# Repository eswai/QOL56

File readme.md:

# QOL56

## 特徴

QOL56は、ほぼ直交格子配列(ortholinear)な56キーのキーボードです。
ortholinearキーボードはplanckが有名ですが、planckよりも2列、8キー多い配列です。
親指で自然に押せるキーを6キー配置すると必然的に14列必要になりました。
その結果、親指でシフト、スペース、エンター、レイヤー切り替えなど頻度の高いキー操作が可能です。
また、親指シフト入力での使用を念頭において設計しており、現在の親指シフト入力をする上での様々な課題を解決し、最新のキーボードトレンドを取り込んで、接続するだけで快適に親指シフト入力できることを目指すキーボードです。

## 親指シフト入力に対応

親指シフト入力のユーザーは、高価な専用キーボードを購入したり、いわゆるB割れしているキーボードを探したり、orz配列という右手のキーを1列ずらすなどの努力をしていますが、自作することで親指シフトに最適なキーボードを実現することが目的です。
同時に旧来のrow staggeredの非対称キー配置から脱却し、より効率の良い配列へ移行することもめざしています。
親指シフトなどの同時押しでは特にキー配置が左右対称であるべきだと考えています。
もっとエルゴノミックなキー配列はたくさんあるのですが、まずはシンプルで扱いやすそうな直交格子配列にしてみました。
親指との同時押しが快適にできるように親指で押す6キーを0.25U下げて配置しています。

さらに親指シフト入力をするために通常は追加でソフトウェアのインストールが必要です。
親指シフトするためのソフトとして、例えばやまぶきRやLacailleなどのソフトがあります。
自作キーボード用のファームウェアQMKは非常に高機能なので、ファームウェアレベルでの親指シフト入力をサポートしました。
追加ソフトなしでの親指シフトの入力が可能です。

## LED

バックライトやアンダーグロウのLEDはかっこよくて所有欲を満たしてくれるものですので、71個(バックライト56個、アンダーグロー15個)のフルカラーLEDを搭載して、QMKのアニメーションをフルに楽しめるようになっています。

## 実装面での特徴

* Pro Microをキー下に配置してフットプリントを最小化
* Pro Microと重ならない54キーはソケットを採用してキースイッチを交換可能にした
* コンスルー対応で、Pro Microの脱着が可能
* チルトさせることで全体が厚くならないように配慮

## 制作について

キット販売などはないので、PCBなどの部品をメーカーに制作してもらう必要がありますが、ガーバーファイルやアクリルカットのためのepsファイルを公開しています。
決して初心者向きではありませんが、ある程度知識があれば容易に部品の調達は可能です。

部品一覧表

|部品名|仕様|数量|
|---|---|---|
|PCBトッププレート|1.6mm|1|
|PCB基板|1.6mm|1|
|アクリルボトムプレート3種類|2mm|1 set|
|キースイッチ|MX互換|56|
|キーキャップ|1U|56|
|ねじ|M2 x 4mm|12|
|ねじ|M2 x 10mm|4|
|スペーサ|M2 x 7mm|8|
|Pro Micro|ATmega32U4 5V 16MHz|1|
|ダイオード|1N4148Wまたは1N4148|56|
|Kailh PCB Socket|CPG151101S11|54|
|タクトスイッチ|2極 SMD 4x3x2mm|1|

LEDを付ける場合は以下の部品を用意します。なくても動作します。

|部品名|仕様|数量|
|---|---|---|
|LED|SK6812 mini 3535|56|
|LEDテープ|WS2812|25cm 15個|

参考価格ですが、elecrowにPCB、トッププレート、ボトムプレートの3点をオーダーしましたが、最小単位の5セット、送料込みで$100以下でした。
他にはCherry MX互換のスイッチ、キーキャップ、Pro Micro、ダイオード、ソケット、M2ねじなど自作キーボードでは一般的な部品を採用しています。
また、kicadファイルも公開していますので、自由に改造して自分好みのレイアウトを作っていただくことも可能です。
QMKのコードは [GitHub](https://github.com/eswai/qmk_firmware/tree/master/keyboards/eswai/qol56) にありますので、キーマップの修正が可能です。

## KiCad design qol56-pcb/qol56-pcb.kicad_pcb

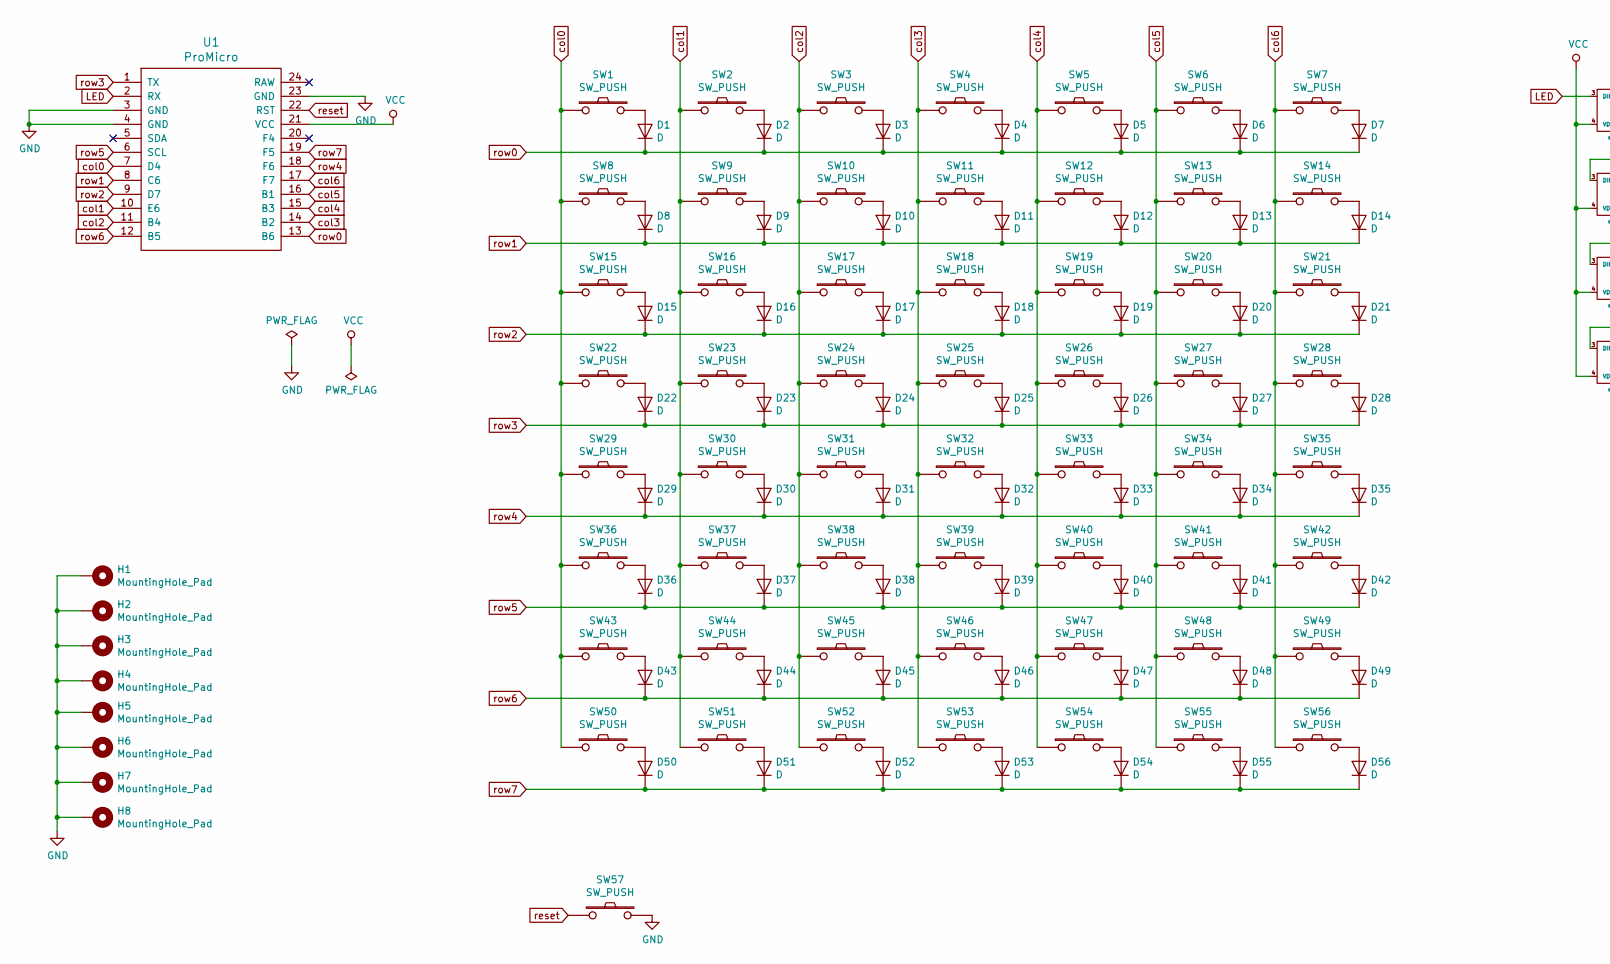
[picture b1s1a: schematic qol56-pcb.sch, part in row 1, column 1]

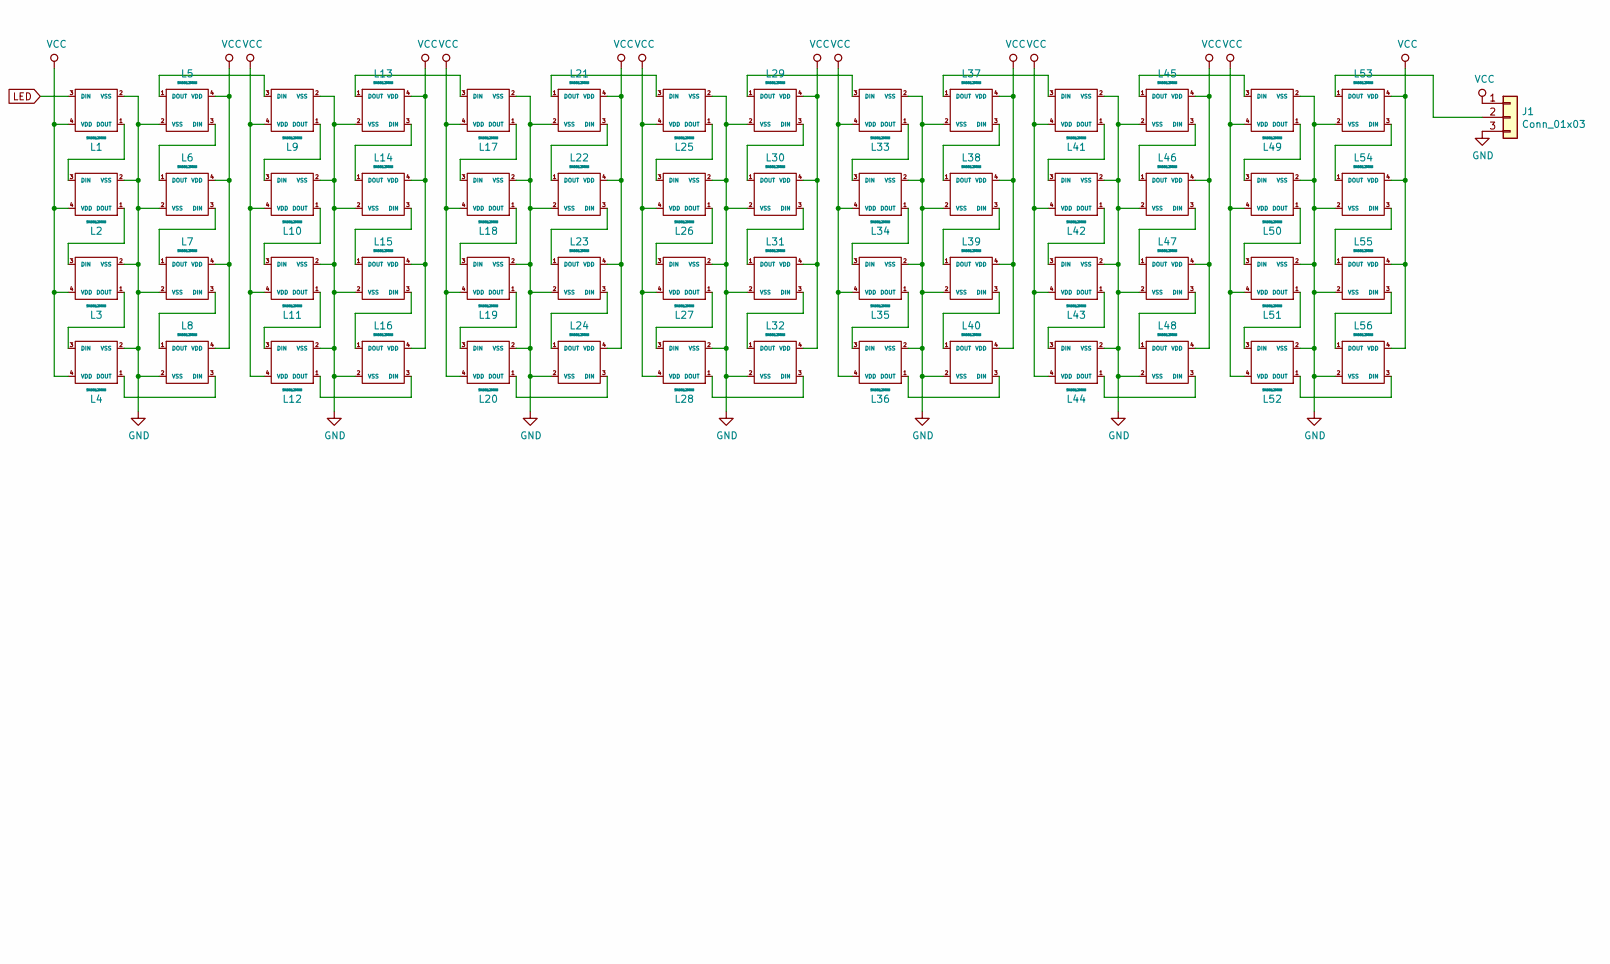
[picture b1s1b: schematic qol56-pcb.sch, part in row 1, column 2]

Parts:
D1, D2, D3, D4, D5, D6, D7, D8, D9, D10, D11, D12, D13, D14, D15, D16, D17, D18, D19, D20, D21, D22, D23, D24, D25, D26, D27, D28, D29, D30, D31, D32, D33, D34, D35, D36, D37, D38, D39, D40, D41, D42, D43, D44, D45, D46, D47, D48, D49, D50, D51, D52, D53, D54, D55, D56: D; Diode-dual
H1, H2, H3, H4, H5, H6, H7, H8: MountingHole_Pad; MountingHole_4mm_Pad
J1: Conn_01x03; StripLED_rev
L1, L2, L3, L4, L5, L6, L7, L8, L9, L10, L11, L12, L13, L14, L15, L16, L17, L18, L19, L20, L21, L22, L23, L24, L25, L26, L27, L28, L29, L30, L31, L32, L33, L34, L35, L36, L37, L38, L39, L40, L41, L42, L43, L44, L45, L46, L47, L48, L49, L50, L51, L52, L53, L54, L55, L56: SK6812MINI; SK6812MINI_rev
SW1, SW2: SW_PUSH; MX_PCB_100H
SW3, SW4, SW5, SW6, SW7, SW8, SW9, SW10, SW11, SW12, SW13, SW14, SW15, SW16, SW17, SW18, SW19, SW20, SW21, SW22, SW23, SW24, SW25, SW26, SW27, SW28, SW29, SW30, SW31, SW32, SW33, SW34, SW35, SW36, SW37, SW38, SW39, SW40, SW41, SW42, SW43, SW44, SW45, SW46, SW47, SW48, SW49, SW50, SW51, SW52, SW53, SW54, SW55, SW56: SW_PUSH; CherryMX_Hotswap
SW57: SW_PUSH; SMD 2Pin 3X4MM Tactile Tact Push Button
U1: ProMicro; ArduinoProMicro

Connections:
GND: H1.1, H2.1, H3.1, H4.1, H5.1, H6.1, H7.1, H8.1, J1.3, L1.2 (VSS), L2.2 (VSS), L3.2 (VSS), L4.2 (VSS), L5.2 (VSS), L6.2 (VSS), L7.2 (VSS), L8.2 (VSS), L9.2 (VSS), L10.2 (VSS), L11.2 (VSS), L12.2 (VSS), L13.2 (VSS), L14.2 (VSS), L15.2 (VSS), L16.2 (VSS), L17.2 (VSS), L18.2 (VSS), L19.2 (VSS), L20.2 (VSS), L21.2 (VSS), L22.2 (VSS), L23.2 (VSS), L24.2 (VSS), L25.2 (VSS), L26.2 (VSS), L27.2 (VSS), L28.2 (VSS), L29.2 (VSS), L30.2 (VSS), L31.2 (VSS), L32.2 (VSS), L33.2 (VSS), L34.2 (VSS), L35.2 (VSS), L36.2 (VSS), L37.2 (VSS), L38.2 (VSS), L39.2 (VSS), L40.2 (VSS), L41.2 (VSS), L42.2 (VSS), L43.2 (VSS), L44.2 (VSS), L45.2 (VSS), L46.2 (VSS), L47.2 (VSS), L48.2 (VSS), L49.2 (VSS), L50.2 (VSS), L51.2 (VSS), L52.2 (VSS), L53.2 (VSS), L54.2 (VSS), L55.2 (VSS), L56.2 (VSS), SW57.2, U1.3 (GND), U1.4 (GND), U1.23 (GND)
LED: L1.3 (DIN), U1.2 (RX)
unnamed: D1.2 (A), SW1.2
unnamed: D2.2 (A), SW2.2
unnamed: D3.2 (A), SW3.2
unnamed: D4.2 (A), SW4.2
unnamed: D5.2 (A), SW5.2
unnamed: D6.2 (A), SW6.2
unnamed: D7.2 (A), SW7.2
unnamed: D8.2 (A), SW8.2
unnamed: D9.2 (A), SW9.2
unnamed: D10.2 (A), SW10.2
unnamed: D11.2 (A), SW11.2
unnamed: D12.2 (A), SW12.2
unnamed: D13.2 (A), SW13.2
unnamed: D14.2 (A), SW14.2
unnamed: D15.2 (A), SW15.2
unnamed: D16.2 (A), SW16.2
unnamed: D17.2 (A), SW17.2
unnamed: D18.2 (A), SW18.2
unnamed: D19.2 (A), SW19.2
unnamed: D20.2 (A), SW20.2
unnamed: D21.2 (A), SW21.2
unnamed: D22.2 (A), SW22.2
unnamed: D23.2 (A), SW23.2
unnamed: D24.2 (A), SW24.2
unnamed: D25.2 (A), SW25.2
unnamed: D26.2 (A), SW26.2
unnamed: D27.2 (A), SW27.2
unnamed: D28.2 (A), SW28.2
unnamed: D29.2 (A), SW29.2
unnamed: D30.2 (A), SW30.2
unnamed: D31.2 (A), SW31.2
unnamed: D32.2 (A), SW32.2
unnamed: D33.2 (A), SW33.2
unnamed: D34.2 (A), SW34.2
unnamed: D35.2 (A), SW35.2
unnamed: D36.2 (A), SW36.2
unnamed: D37.2 (A), SW37.2
unnamed: D38.2 (A), SW38.2
unnamed: D39.2 (A), SW39.2
unnamed: D40.2 (A), SW40.2
unnamed: D41.2 (A), SW41.2
unnamed: D42.2 (A), SW42.2
unnamed: D43.2 (A), SW43.2
unnamed: D44.2 (A), SW44.2
unnamed: D45.2 (A), SW45.2
unnamed: D46.2 (A), SW46.2
unnamed: D47.2 (A), SW47.2
unnamed: D48.2 (A), SW48.2
unnamed: D49.2 (A), SW49.2
unnamed: D50.2 (A), SW50.2
unnamed: D51.2 (A), SW51.2
unnamed: D52.2 (A), SW52.2
unnamed: D53.2 (A), SW53.2
unnamed: D54.2 (A), SW54.2
unnamed: D55.2 (A), SW55.2
unnamed: D56.2 (A), SW56.2
unnamed: J1.2, L53.1 (DOUT)
unnamed: L1.1 (DOUT), L2.3 (DIN)
unnamed: L2.1 (DOUT), L3.3 (DIN)
unnamed: L3.1 (DOUT), L4.3 (DIN)
unnamed: L4.1 (DOUT), L8.3 (DIN)
unnamed: L5.1 (DOUT), L9.3 (DIN)
unnamed: L5.3 (DIN), L6.1 (DOUT)
unnamed: L6.3 (DIN), L7.1 (DOUT)
unnamed: L7.3 (DIN), L8.1 (DOUT)
unnamed: L10.1 (DOUT), L11.3 (DIN)
unnamed: L9.1 (DOUT), L10.3 (DIN)
unnamed: L11.1 (DOUT), L12.3 (DIN)
unnamed: L12.1 (DOUT), L16.3 (DIN)
unnamed: L13.1 (DOUT), L17.3 (DIN)
unnamed: L13.3 (DIN), L14.1 (DOUT)
unnamed: L14.3 (DIN), L15.1 (DOUT)
unnamed: L15.3 (DIN), L16.1 (DOUT)
unnamed: L17.1 (DOUT), L18.3 (DIN)
unnamed: L18.1 (DOUT), L19.3 (DIN)
unnamed: L19.1 (DOUT), L20.3 (DIN)
unnamed: L20.1 (DOUT), L24.3 (DIN)
unnamed: L21.1 (DOUT), L25.3 (DIN)
unnamed: L21.3 (DIN), L22.1 (DOUT)
unnamed: L22.3 (DIN), L23.1 (DOUT)
unnamed: L23.3 (DIN), L24.1 (DOUT)
unnamed: L25.1 (DOUT), L26.3 (DIN)
unnamed: L26.1 (DOUT), L27.3 (DIN)
unnamed: L27.1 (DOUT), L28.3 (DIN)
unnamed: L28.1 (DOUT), L32.3 (DIN)
unnamed: L29.1 (DOUT), L33.3 (DIN)
unnamed: L29.3 (DIN), L30.1 (DOUT)
unnamed: L30.3 (DIN), L31.1 (DOUT)
unnamed: L31.3 (DIN), L32.1 (DOUT)
unnamed: L33.1 (DOUT), L34.3 (DIN)
unnamed: L34.1 (DOUT), L35.3 (DIN)
unnamed: L35.1 (DOUT), L36.3 (DIN)
unnamed: L36.1 (DOUT), L40.3 (DIN)
unnamed: L37.1 (DOUT), L41.3 (DIN)
unnamed: L37.3 (DIN), L38.1 (DOUT)
unnamed: L38.3 (DIN), L39.1 (DOUT)
unnamed: L39.3 (DIN), L40.1 (DOUT)
unnamed: L41.1 (DOUT), L42.3 (DIN)
unnamed: L42.1 (DOUT), L43.3 (DIN)
unnamed: L43.1 (DOUT), L44.3 (DIN)
unnamed: L44.1 (DOUT), L48.3 (DIN)
unnamed: L45.1 (DOUT), L49.3 (DIN)
unnamed: L45.3 (DIN), L46.1 (DOUT)
unnamed: L46.3 (DIN), L47.1 (DOUT)
unnamed: L47.3 (DIN), L48.1 (DOUT)
unnamed: L49.1 (DOUT), L50.3 (DIN)
unnamed: L50.1 (DOUT), L51.3 (DIN)
unnamed: L51.1 (DOUT), L52.3 (DIN)
unnamed: L52.1 (DOUT), L56.3 (DIN)
unnamed: L53.3 (DIN), L54.1 (DOUT)
unnamed: L54.3 (DIN), L55.1 (DOUT)
unnamed: L55.3 (DIN), L56.1 (DOUT)
VCC: J1.1, L1.4 (VDD), L2.4 (VDD), L3.4 (VDD), L4.4 (VDD), L5.4 (VDD), L6.4 (VDD), L7.4 (VDD), L8.4 (VDD), L9.4 (VDD), L10.4 (VDD), L11.4 (VDD), L12.4 (VDD), L13.4 (VDD), L14.4 (VDD), L15.4 (VDD), L16.4 (VDD), L17.4 (VDD), L18.4 (VDD), L19.4 (VDD), L20.4 (VDD), L21.4 (VDD), L22.4 (VDD), L23.4 (VDD), L24.4 (VDD), L25.4 (VDD), L26.4 (VDD), L27.4 (VDD), L28.4 (VDD), L29.4 (VDD), L30.4 (VDD), L31.4 (VDD), L32.4 (VDD), L33.4 (VDD), L34.4 (VDD), L35.4 (VDD), L36.4 (VDD), L37.4 (VDD), L38.4 (VDD), L39.4 (VDD), L40.4 (VDD), L41.4 (VDD), L42.4 (VDD), L43.4 (VDD), L44.4 (VDD), L45.4 (VDD), L46.4 (VDD), L47.4 (VDD), L48.4 (VDD), L49.4 (VDD), L50.4 (VDD), L51.4 (VDD), L52.4 (VDD), L53.4 (VDD), L54.4 (VDD), L55.4 (VDD), L56.4 (VDD), U1.21 (VCC)
col0: SW1.1, SW8.1, SW15.1, SW22.1, SW29.1, SW36.1, SW43.1, SW50.1, U1.7 (D4)
col1: SW2.1, SW9.1, SW16.1, SW23.1, SW30.1, SW37.1, SW44.1, SW51.1, U1.10 (E6)
col2: SW3.1, SW10.1, SW17.1, SW24.1, SW31.1, SW38.1, SW45.1, SW52.1, U1.11 (B4)
col3: SW4.1, SW11.1, SW18.1, SW25.1, SW32.1, SW39.1, SW46.1, SW53.1, U1.14 (B2)
col4: SW5.1, SW12.1, SW19.1, SW26.1, SW33.1, SW40.1, SW47.1, SW54.1, U1.15 (B3)
col5: SW6.1, SW13.1, SW20.1, SW27.1, SW34.1, SW41.1, SW48.1, SW55.1, U1.16 (B1)
col6: SW7.1, SW14.1, SW21.1, SW28.1, SW35.1, SW42.1, SW49.1, SW56.1, U1.17 (F7)
reset: SW57.1, U1.22 (RST)
row0: D1.1 (K), D2.1 (K), D3.1 (K), D4.1 (K), D5.1 (K), D6.1 (K), D7.1 (K), U1.13 (B6)
row1: D8.1 (K), D9.1 (K), D10.1 (K), D11.1 (K), D12.1 (K), D13.1 (K), D14.1 (K), U1.8 (C6)
row2: D15.1 (K), D16.1 (K), D17.1 (K), D18.1 (K), D19.1 (K), D20.1 (K), D21.1 (K), U1.9 (D7)
row3: D22.1 (K), D23.1 (K), D24.1 (K), D25.1 (K), D26.1 (K), D27.1 (K), D28.1 (K), U1.1 (TX)
row4: D29.1 (K), D30.1 (K), D31.1 (K), D32.1 (K), D33.1 (K), D34.1 (K), D35.1 (K), U1.18 (F6)
row5: D36.1 (K), D37.1 (K), D38.1 (K), D39.1 (K), D40.1 (K), D41.1 (K), D42.1 (K), U1.6 (SCL)
row6: D43.1 (K), D44.1 (K), D45.1 (K), D46.1 (K), D47.1 (K), D48.1 (K), D49.1 (K), U1.12 (B5)
row7: D50.1 (K), D51.1 (K), D52.1 (K), D53.1 (K), D54.1 (K), D55.1 (K), D56.1 (K), U1.19 (F5)

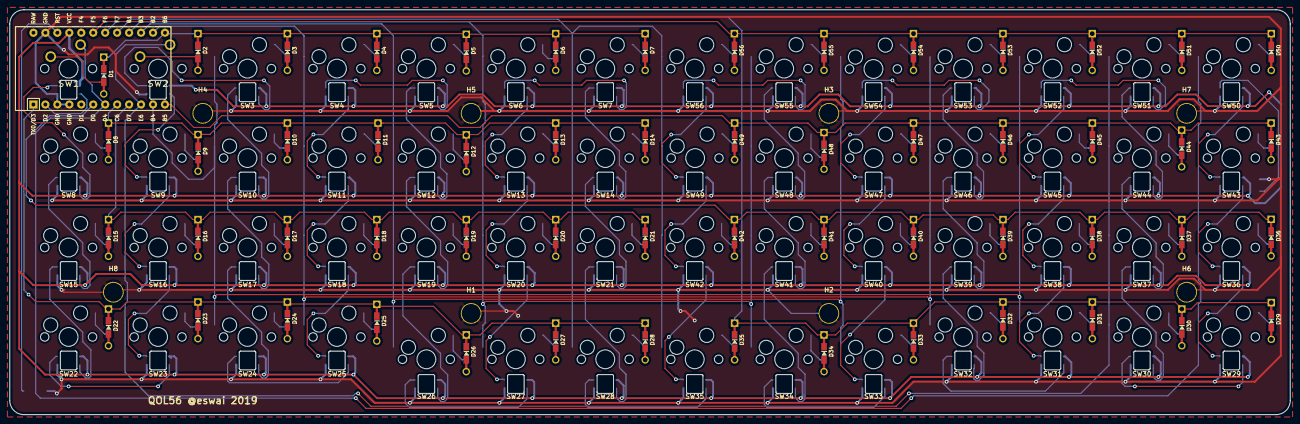
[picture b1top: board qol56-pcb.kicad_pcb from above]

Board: 2 copper layers, 272.0 x 86.0 mm, 179 parts (1 on the bottom side), 131 nets.

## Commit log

2019-03-16 link to firmware
2019-03-16 PCB screenshots
2019-03-17 Parts
2019-03-23 Photos added
2019-04-15 Screws
